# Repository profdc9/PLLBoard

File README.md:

# PLL Board
This is a PLL dev board based on the SI5351A and the common breakout board.  It adds pads so that a TCXO can be added easily to be PCB.

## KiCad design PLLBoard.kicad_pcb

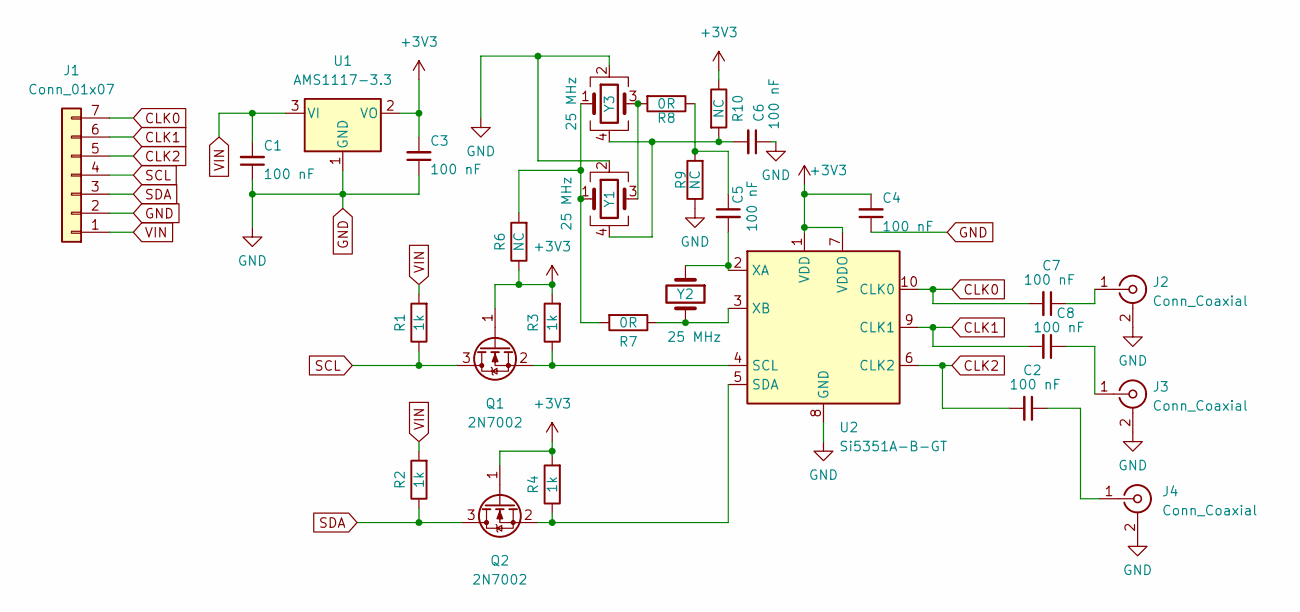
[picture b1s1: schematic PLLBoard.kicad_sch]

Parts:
C1, C2, C3, C4, C5, C6, C7, C8: 100 nF; C_0805_2012Metric_Pad1.18x1.45mm_HandSolder; LCSC C49678
J1: Conn_01x07; PinSocket_1x07_P2.54mm_Vertical
J2, J3, J4: Conn_Coaxial; SMA_Amphenol_132289_EdgeMount_Wide
Q1, Q2: 2N7002; SOT-23; LCSC C8545
R1, R2, R3, R4: 1k; R_0805_2012Metric_Pad1.20x1.40mm_HandSolder; LCSC C17513
R6, R9, R10: NC; R_0805_2012Metric_Pad1.20x1.40mm_HandSolder
R7, R8: 0R; R_0805_2012Metric_Pad1.20x1.40mm_HandSolder; LCSC C17477
U1: AMS1117-3.3; SOT-223-3_TabPin2; LCSC C6186
U2: Si5351A-B-GT; MSOP-10_3x3mm_P0.5mm; LCSC C1509083
Y1: 25 MHz; Crystal_SMD_3225-4Pin_3.2x2.5mm_HandSoldering; LCSC C9006
Y2: 25 MHz; Crystal_HC49-U_Vertical
Y3: 25 MHz; Crystal_SMD_2520-4Pin_2.5x2.0mm

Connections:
+3V3: C3.2, C4.2, Q1.1 (G), Q2.1 (G), R3.2, R4.2, R6.1, R10.1, U1.2 (VO), U2.1 (VDD), U2.7 (VDDO)
CLK0: C7.2, J1.7, U2.10 (CLK0)
CLK1: C8.2, J1.6, U2.9 (CLK1)
CLK2: C2.2, J1.5, U2.6 (CLK2)
GND: C1.1, C3.1, C4.1, C6.1, J1.2, J2.2 (Ext), J3.2 (Ext), J4.2 (Ext), R9.1, U1.1 (GND), U2.8 (GND), Y1.2, Y3.2
unnamed: C2.1, J4.1 (In)
unnamed: C5.1, R8.1, R9.2
unnamed: C5.2, U2.2 (XA), Y2.1
unnamed: C6.2, R10.2, Y1.4, Y3.4
unnamed: C7.1, J2.1 (In)
unnamed: C8.1, J3.1 (In)
unnamed: Q1.2 (S), R3.1, U2.4 (SCL)
unnamed: Q2.2 (S), R4.1, U2.5 (SDA)
unnamed: R6.2, R7.2, Y1.1, Y3.1
unnamed: R7.1, U2.3 (XB), Y2.2
unnamed: R8.2, Y1.3, Y3.3
SCL: J1.4, Q1.3 (D), R1.1
SDA: J1.3, Q2.3 (D), R2.1
VIN: C1.2, J1.1, R1.2, R2.2, U1.3 (VI)

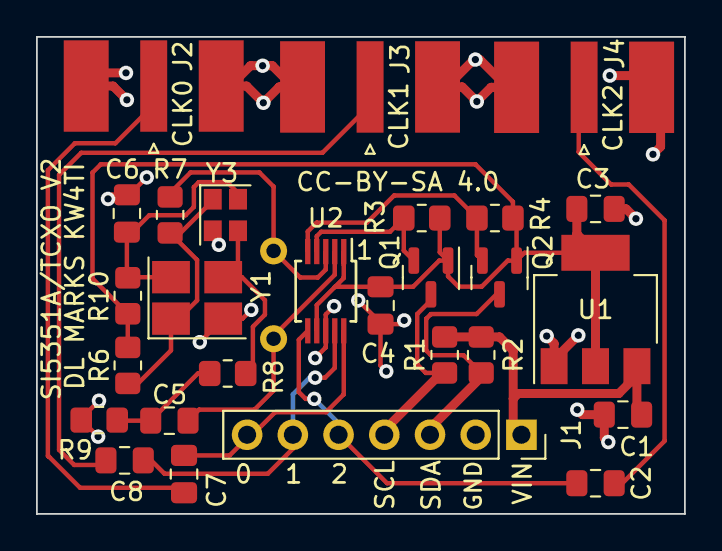
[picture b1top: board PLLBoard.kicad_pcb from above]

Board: 2 copper layers, 36.0 x 26.5 mm, 28 parts (1 on the bottom side), 19 nets.

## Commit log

2023-11-11 Initial JLCPCB build
2023-11-24 Shrink PLL board, remove resistor

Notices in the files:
PLLBoard.kicad_pcb:
CC-BY-SA 4.0
